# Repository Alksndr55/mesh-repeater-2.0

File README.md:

<div align="center">

# Mesh Repeater

### Плата LoRa-репитера для MeshCore и Meshtastic

**v2.10 · POWER + LOGIC + SHIELD · 90 × 60 мм**

Солнечное питание · Na-ion 1S / LTO 2S · аппаратный watchdog

[Скачать готовый комплект](https://github.com/Alksndr55/mesh-repeater-2.0/releases/download/v2.10/Mesh_Repeater_v2.10_KiCad.zip) · [Релиз v2.10](https://github.com/Alksndr55/mesh-repeater-2.0/releases/tag/v2.10) · [Одноплатная версия v1](https://github.com/Alksndr55/mesh-repeater)

*Mesh Repeater v2.10 в сборе, вариант Na-ion 1S с COLD. Сверху LOGIC, в середине SHIELD, снизу POWER.*

</div>

Mesh Repeater v2 переносит электрическую часть ведущей версии v1 на две рабочие платы размером **90 × 60 мм**. Зарядник и преобразователь питания находятся на POWER, радиочасть и управление — на LOGIC. Между ними предусмотрена отдельная плата экрана SHIELD.

**Главные цели проекта — максимальное энергосбережение и работа в суровых сибирских зимах.**

Такое исполнение уменьшает площадь основания устройства. Межплатное соединение, стойки и крепёж описаны в проекте; исходники KiCad, перечень компонентов и материалы для сборки входят в готовый комплект.

## Что предусмотрено

| Узел | Назначение |
|---|---|
| **nRF52840 + LoRa** | Доработанный NiceNano, модуль HT-RA62 на SX1262, антенный разъём SMA и место под фильтр FL1. |
| **Солнечный зарядник** | CN3722 с настройкой рабочей точки солнечной панели. |
| **Na-ion 1S или LTO 2S** | Три варианта комплектации: Na-ion 1S с COLD, Na-ion 1S без COLD, LTO 2S с пассивной балансировкой. |
| **Питание 3,3 В** | Повышающе-понижающий TPS63802, двухступенчатый LC-фильтр и отдельная ветвь питания радиомодуля. |
| **Контроль аккумулятора** | INA219 измеряет напряжение и ток в основном тракте аккумулятора. |
| **Часы и watchdog** | DS3231M с резервом от CR2032; ATtiny13A следит за активностью TXEN и может сбросить основной процессор. |
| **Подключение и обслуживание** | Разъём внешнего GPS, I²C и UART с логикой 3,3 В, AVR ISP, кнопки USER/RESET и контрольные точки. |

## Три платы одного комплекта

| Плата | Что на ней |
|---|---|
| **POWER** | Заряд аккумулятора, COLD или балансиры LTO, преобразователь 3,3 В и LC-фильтр. |
| **LOGIC** | NiceNano, LoRa-модуль, часы, watchdog и интерфейсы. |
| **SHIELD** | Промежуточная плата экрана с GND-плоскостью и окном межплатного соединителя. |

<details>
<summary><strong>Отдельные платы и виды с двух сторон</strong></summary>

| LOGIC — связь и управление | POWER — заряд и питание |
|:---:|:---:|
|  |  |

*3D-рендеры отдельных плат со стороны компонентов. Комплектацию для выбранного варианта определяет BOM.*

| LOGIC — обратная сторона | POWER — обратная сторона |
|:---:|:---:|
|  |  |

</details>

В собранном устройстве LOGIC обращена компонентами вниз. Используется заданная пара межплатных разъёмов; обычная незеркальная розетка не является заменой J201. Размеры стоек и порядок сборки приведены в [описании механики](v2/docs/MECHANICS_RU.md).

### Опциональный фильтр антенны

На LOGIC предусмотрено место **FL1** для полосового SAW-фильтра **S869M000S003**. Он ослабляет внеполосные сигналы. В полосе 868–870 МГц паспортные потери составляют до 2,5 дБ. Штатный тракт проходит через медную перемычку **NT1**. Перед монтажом FL1 перемычку разрезают по инструкции и ограничивают мощность на входе фильтра до **+13 дБм**.

Рабочая температура этого фильтра **−10…+65 °C**. Для более холодных установок сохраняют штатный обход NT1. [Паспорт фильтра](https://abracon.com/datasheets/AEL-Crystals/PN/S869M000S003.pdf) · [Монтаж FL1](docs/ASSEMBLY_COMMON_RU.md)

## Совместимость с MeshCore и Meshtastic

Радиомодуль HT-RA62 (SX1262 с TCXO) подключён по распиновке **FakeTec / ProMicro nRF52840**. Для обеих версий платы подходят следующие профили прошивок.

| Прошивка | Профиль | Конфигурация |
|---|---|---|
| **MeshCore** | ProMicro nRF52840, сборка `ProMicro_repeater` | [MeshCore ProMicro](https://github.com/meshcore-dev/MeshCore/blob/repeater-v1.18.0/variants/promicro/platformio.ini#L40-L53) |
| **Meshtastic** | NRF52 Pro-micro DIY с TCXO, сборка `nrf52_promicro_diy_tcxo` | [Meshtastic ProMicro TCXO](https://github.com/meshtastic/firmware/blob/v2.7.26.54e0d8d/variants/nrf52840/diy/nrf52_promicro_diy_tcxo/platformio.ini) |

Совместимость проверена по распиновке и конфигурациям сборок. Показания напряжения аккумулятора калибруют под делитель платы **1:2**. Для Na-ion 1S и LTO 2S шкалу процента заряда адаптируют под химию и число ячеек. При подключении внешнего UART к J5 сверяют назначение RX и TX с выбранной прошивкой.

## Варианты сборки

| Вариант | Комплектация |
|---|---|
| **Na-ion 1S · COLD** | Узел температурного ограничения зарядного тока установлен. |
| **Na-ion 1S · без COLD** | Сборка без узла COLD. |
| **LTO · 2S** | Две последовательные ячейки LTO и пассивные балансиры. |

Вариант задаётся номиналами и составом деталей по BOM. Это выбор при сборке, а не переключение химии аккумулятора одной перемычкой. Условия заряда выбирают по паспорту конкретных ячеек; схема LTO не заменяет полноценную BMS.

### COLD — ограничение тока заряда на холоде

В сборке Na-ion 1S с COLD датчик TH1 на POWER задаёт температурный режим солнечного зарядника CN3722. При охлаждении схема включает дополнительный шунт R56 в цепь измерения тока. Расчётный предел зарядного тока снижается примерно с **0,67 А до 0,10 А**. При потеплении возвращается обычный режим.

Расчётный порог снижения тока — **−17,4 °C**, возврата — **−14,5 °C**. Разница между порогами помогает избежать частых переключений при колебаниях температуры. Один датчик TH1 устанавливают на плате или выносят к аккумулятору. Допустимый ток и температуру заряда сверяют с паспортом конкретной ячейки. [Общая инструкция по сборке](docs/ASSEMBLY_COMMON_RU.md)

### Watchdog — автоматический перезапуск репитера

Отдельный ATtiny13A на LOGIC с прошивкой watchdog v1.00 следит за сигналом **TXEN**, который показывает включение передатчика LoRa. Каждое новое включение передатчика запускает отсчёт заново. Между событиями контроллер спит в режиме Power-down. Когда время ожидания истекает, ATtiny13A подаёт импульс RESET на nRF52840. После сброса выбранная прошивка загружается заново и инициализирует радиомодуль.

При 3,3 В и комнатной температуре расчётные ориентиры составляют около **3,5 часа** ожидания и **1,2 секунды** сброса. При длительном молчании радиомодуля или застрявшем высоком TXEN тайм-аут тоже срабатывает. [Подключение и прошивка watchdog](v2/design/watchdog_reference/INTEGRATION_RU.txt)

## От схемы — к детали на плате

В ZIP уже включён **portable NexusBV**. Запуск `START.cmd` открывает меню с CAD и PDF-схемой нужной платы и сборки. Двойной щелчок по обозначению или свободной части тела символа в PDF помогает найти компонент на бордвью.

- Шесть CAD: по **NaIon_COLD** и **LTO_2S** для POWER, LOGIC и SHIELD, с номиналами и DNP. Для SHIELD открывается только CAD.
- PDF-схемы, BOM, инструкции по электрической и механической сборке.
- Проекты KiCad 10 с локальными посадочными местами и всеми используемыми 3D-моделями.
- Watchdog v1.00: исходники, HEX и инструкция прошивки.

## С чего начать

1. Скачайте **Mesh_Repeater_v2.10_KiCad.zip** из [релиза](https://github.com/Alksndr55/mesh-repeater-2.0/releases/tag/v2.10) и полностью распакуйте его.
2. Для просмотра запустите `START.cmd` в Windows; для редактирования откройте [POWER](v2/design/MeshRepeater2_Power/MeshRepeater2_Power.kicad_pro), [LOGIC](v2/design/MeshRepeater2_Logic/MeshRepeater2_Logic.kicad_pro) или [SHIELD](v2/design/MeshRepeater2_Shield/MeshRepeater2_Shield.kicad_pro) в KiCad 10.
3. Выберите вариант аккумулятора и собирайте комплект по [BOM](v2/bom/COMPONENT_BOM.csv), [общей инструкции](docs/ASSEMBLY_COMMON_RU.md) и [описанию механики](v2/docs/MECHANICS_RU.md).

**Перед первым включением:** модуль NiceNano требует указанной в инструкции доработки питания. Перед подключением USB нужно снять шунт **J11**, а вернуть его после отключения USB. J8 и J12 соединены с общей BAT: независимые аккумуляторы к ним одновременно не подключают.

## Документация

[Общая схема PDF](shared/output/pdf/MeshRepeater_schematic.pdf) · [Схема KiCad](shared/schematic/MeshRepeater.kicad_pro) · [Сборка v2](v2/docs/ASSEMBLY_RU.md) · [Аппаратные ограничения](docs/LIMITATIONS_RU.md) · [Изменения выпуска](https://github.com/Alksndr55/mesh-repeater-2.0/releases/tag/v2.10)

<details>
<summary><strong>Статус проекта и проверки</strong></summary>

Это предварительный инженерный выпуск. Для точных файлов v2.10 проверены общая схема, BOM, ERC/DRC, соответствие плат схеме и комплектность архива. Эти проверки не заменяют испытания собранного устройства: дальность связи, автономность, температурные режимы и эффективность экрана здесь не заявляются как измеренные характеристики.

[Отчёт проверок](v2/audit/current/checks.json) · [Экспорт CAD/PDF](v2/audit/current/exports.json) · [Манифест файлов](RELEASE_MANIFEST.json)

</details>

---

**Designed by @Alksndritm** · [Alksndr55](https://github.com/Alksndr55)

Собственные материалы — [CC BY-NC-SA 4.0](v2/LICENSE.md). Сторонние компоненты, модели и программы сохраняют свои лицензии.

Проекты прошивок — [MeshCore](https://github.com/meshcore-dev/MeshCore) и [Meshtastic](https://github.com/meshtastic/firmware).

## Поддержать проект

**Осциллограф Siglent SDS1204X HD.** Пульсации любят прятаться между цифрами мультиметра. Осциллограф поможет их поймать и проверить питание при запуске и передаче.

[Скинуться на осциллограф через Т‑Банк](https://t.tb.ru/pm_short/89zrJmEhG7B)

**Микроскоп Leica IVESTA 3.** У припоя иногда свой план монтажа. Под микроскопом удобнее паять мелкие детали и вовремя замечать перемычки между выводами.

[Скинуться на микроскоп через Сбер](https://messenger.sbrf.ru/sl/KsiFZJu4xBxTLGTPz)

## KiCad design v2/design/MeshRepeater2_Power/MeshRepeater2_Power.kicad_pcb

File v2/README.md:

# Mesh Repeater v2.10

Designed by @Alksndritm. Текущее исполнение общего проекта.
Электрические изменения следуют ведущей v1; разводка адаптирована к двум платам.
Предыдущий опубликованный выпуск от 30.10.2026: [v2.09 на GitHub](https://github.com/Alksndr55/mesh-repeater-2.0/releases/tag/v2.09).
Предыдущая публикация — [v2.06](https://github.com/Alksndr55/mesh-repeater-2.0/releases/tag/v2.06)
(прежнее обозначение A6). Локальная редакция от 06.11.2026 — v2.10. Следующий номер — v2.11.

[POWER](design/MeshRepeater2_Power/MeshRepeater2_Power.kicad_pro) · [LOGIC](design/MeshRepeater2_Logic/MeshRepeater2_Logic.kicad_pro) · [SHIELD](design/MeshRepeater2_Shield/MeshRepeater2_Shield.kicad_pro)

[Общая схема](../shared/schematic/MeshRepeater.kicad_pro) ·
[BOM](bom/COMPONENT_BOM.csv) · [Сборка](docs/ASSEMBLY_RU.md) ·
[Порядок выпуска](../docs/WORKFLOW_RU.md) · [Лицензия](LICENSE.md).

Текущие экспорты находятся в output/current, проверки — в audit/current.
Версия и состав задаются корневым project.json. CAD остаётся редактируемым;
общий процесс выпуска сохраняет геометрию и проверяет соответствие общей схеме.
Опубликованные исторические теги сохраняют свои прежние имена.

Дорожки и GND-переходы приведены к [общим правилам](../docs/ROUTING_RULES_RU.md)
с адаптацией к POWER/LOGIC. Включён [watchdog v1.00](design/watchdog_reference/INTEGRATION_RU.txt)
с каноническими исходником и HEX; LFUSE=0x73, HFUSE=0xFB, ISP 100 мкс.
Локальный архив этого выпуска создаётся в `../releases/v2.10/`.
[Результат разводки и исключения сетки](../docs/ROUTING_RESULT_RU.md).

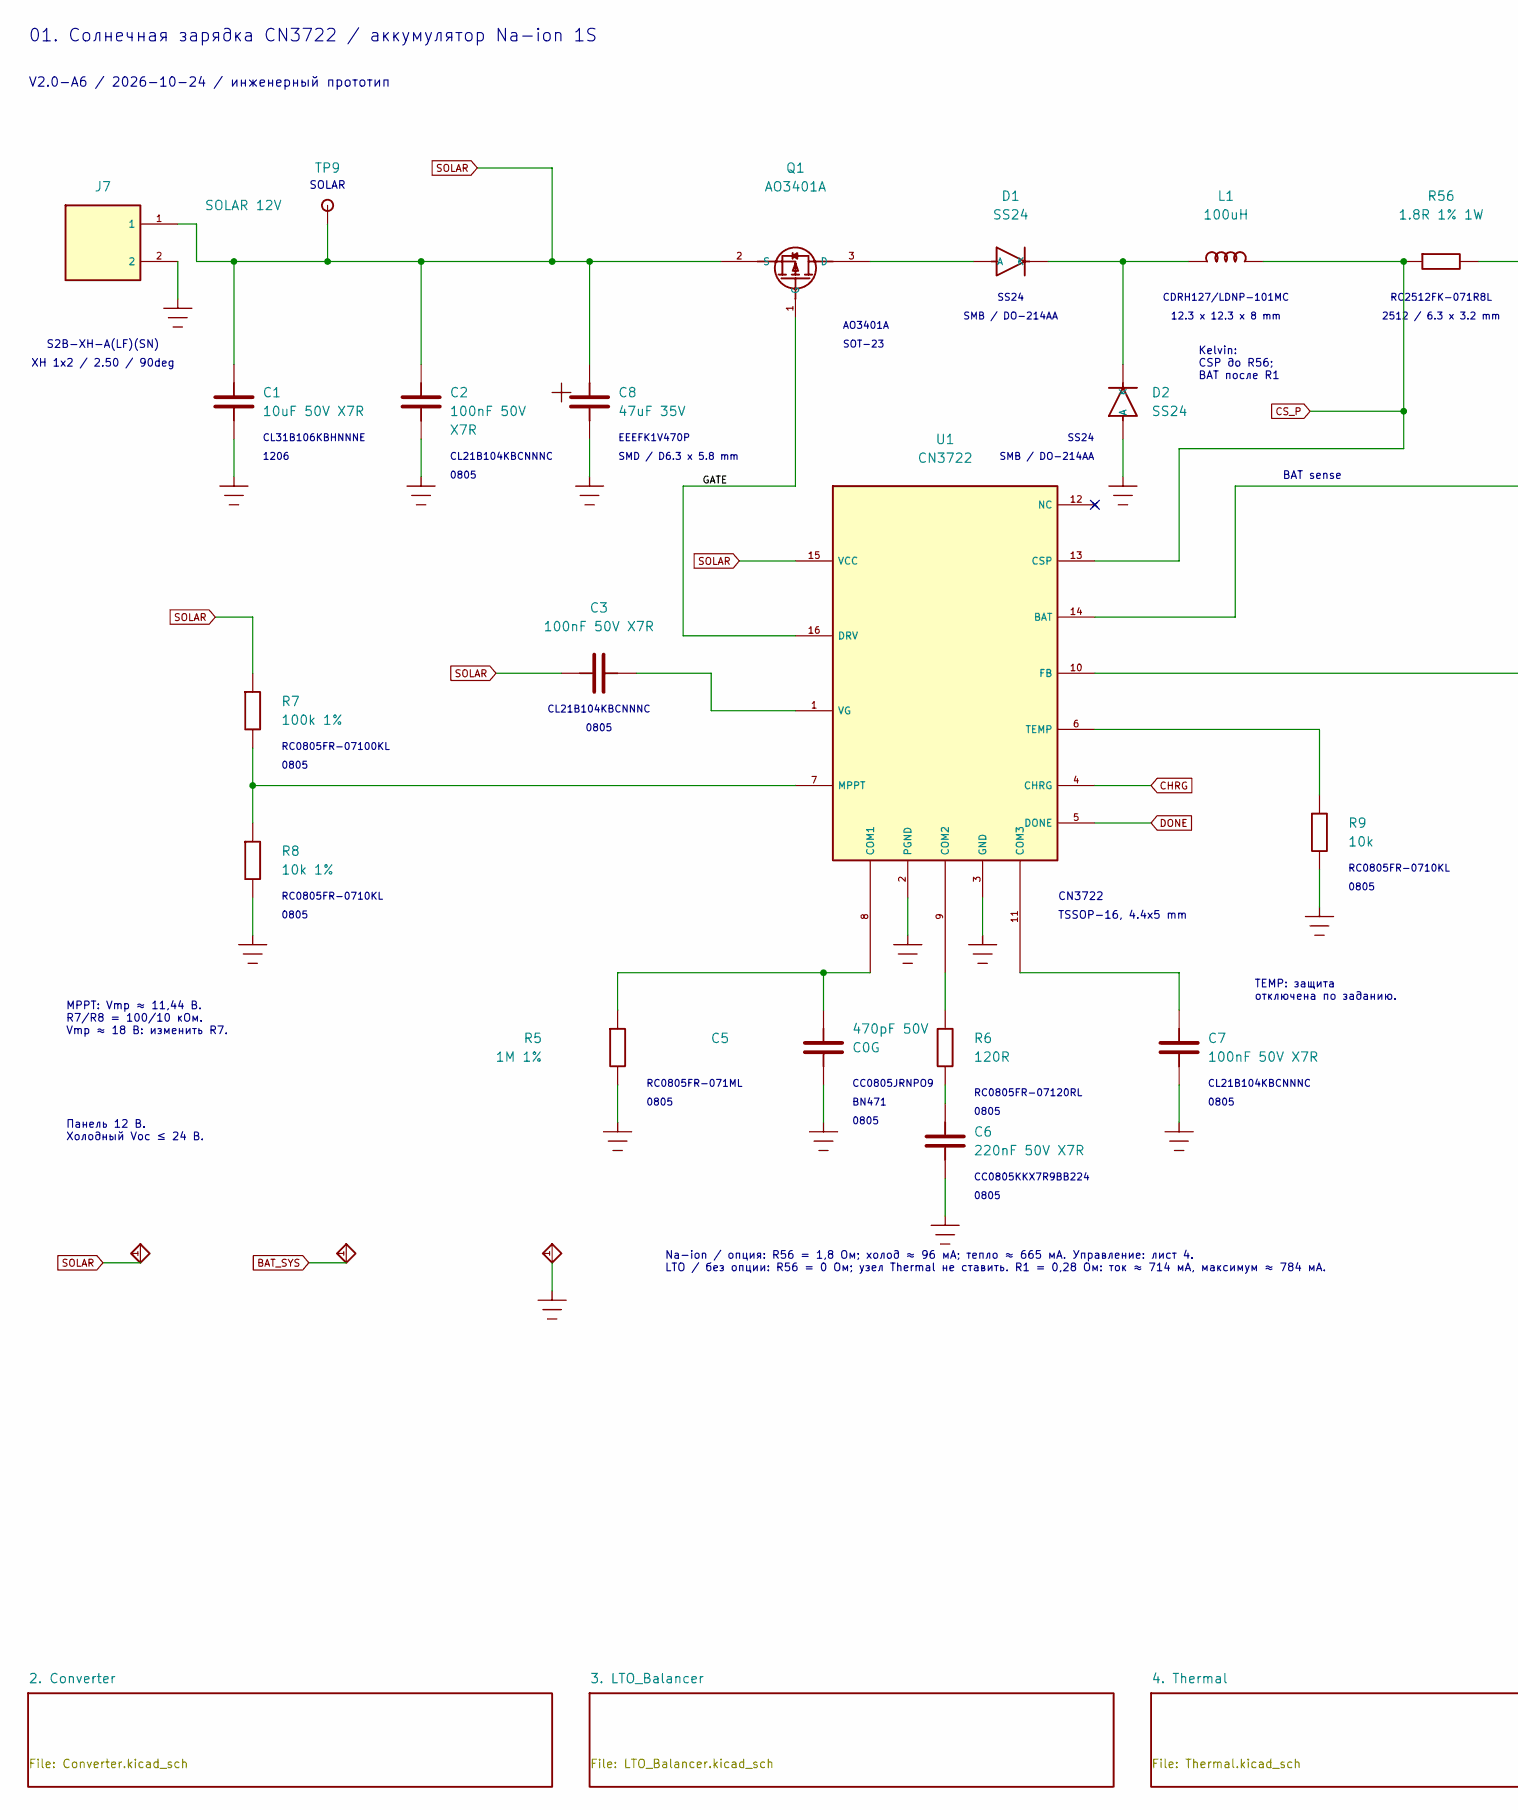
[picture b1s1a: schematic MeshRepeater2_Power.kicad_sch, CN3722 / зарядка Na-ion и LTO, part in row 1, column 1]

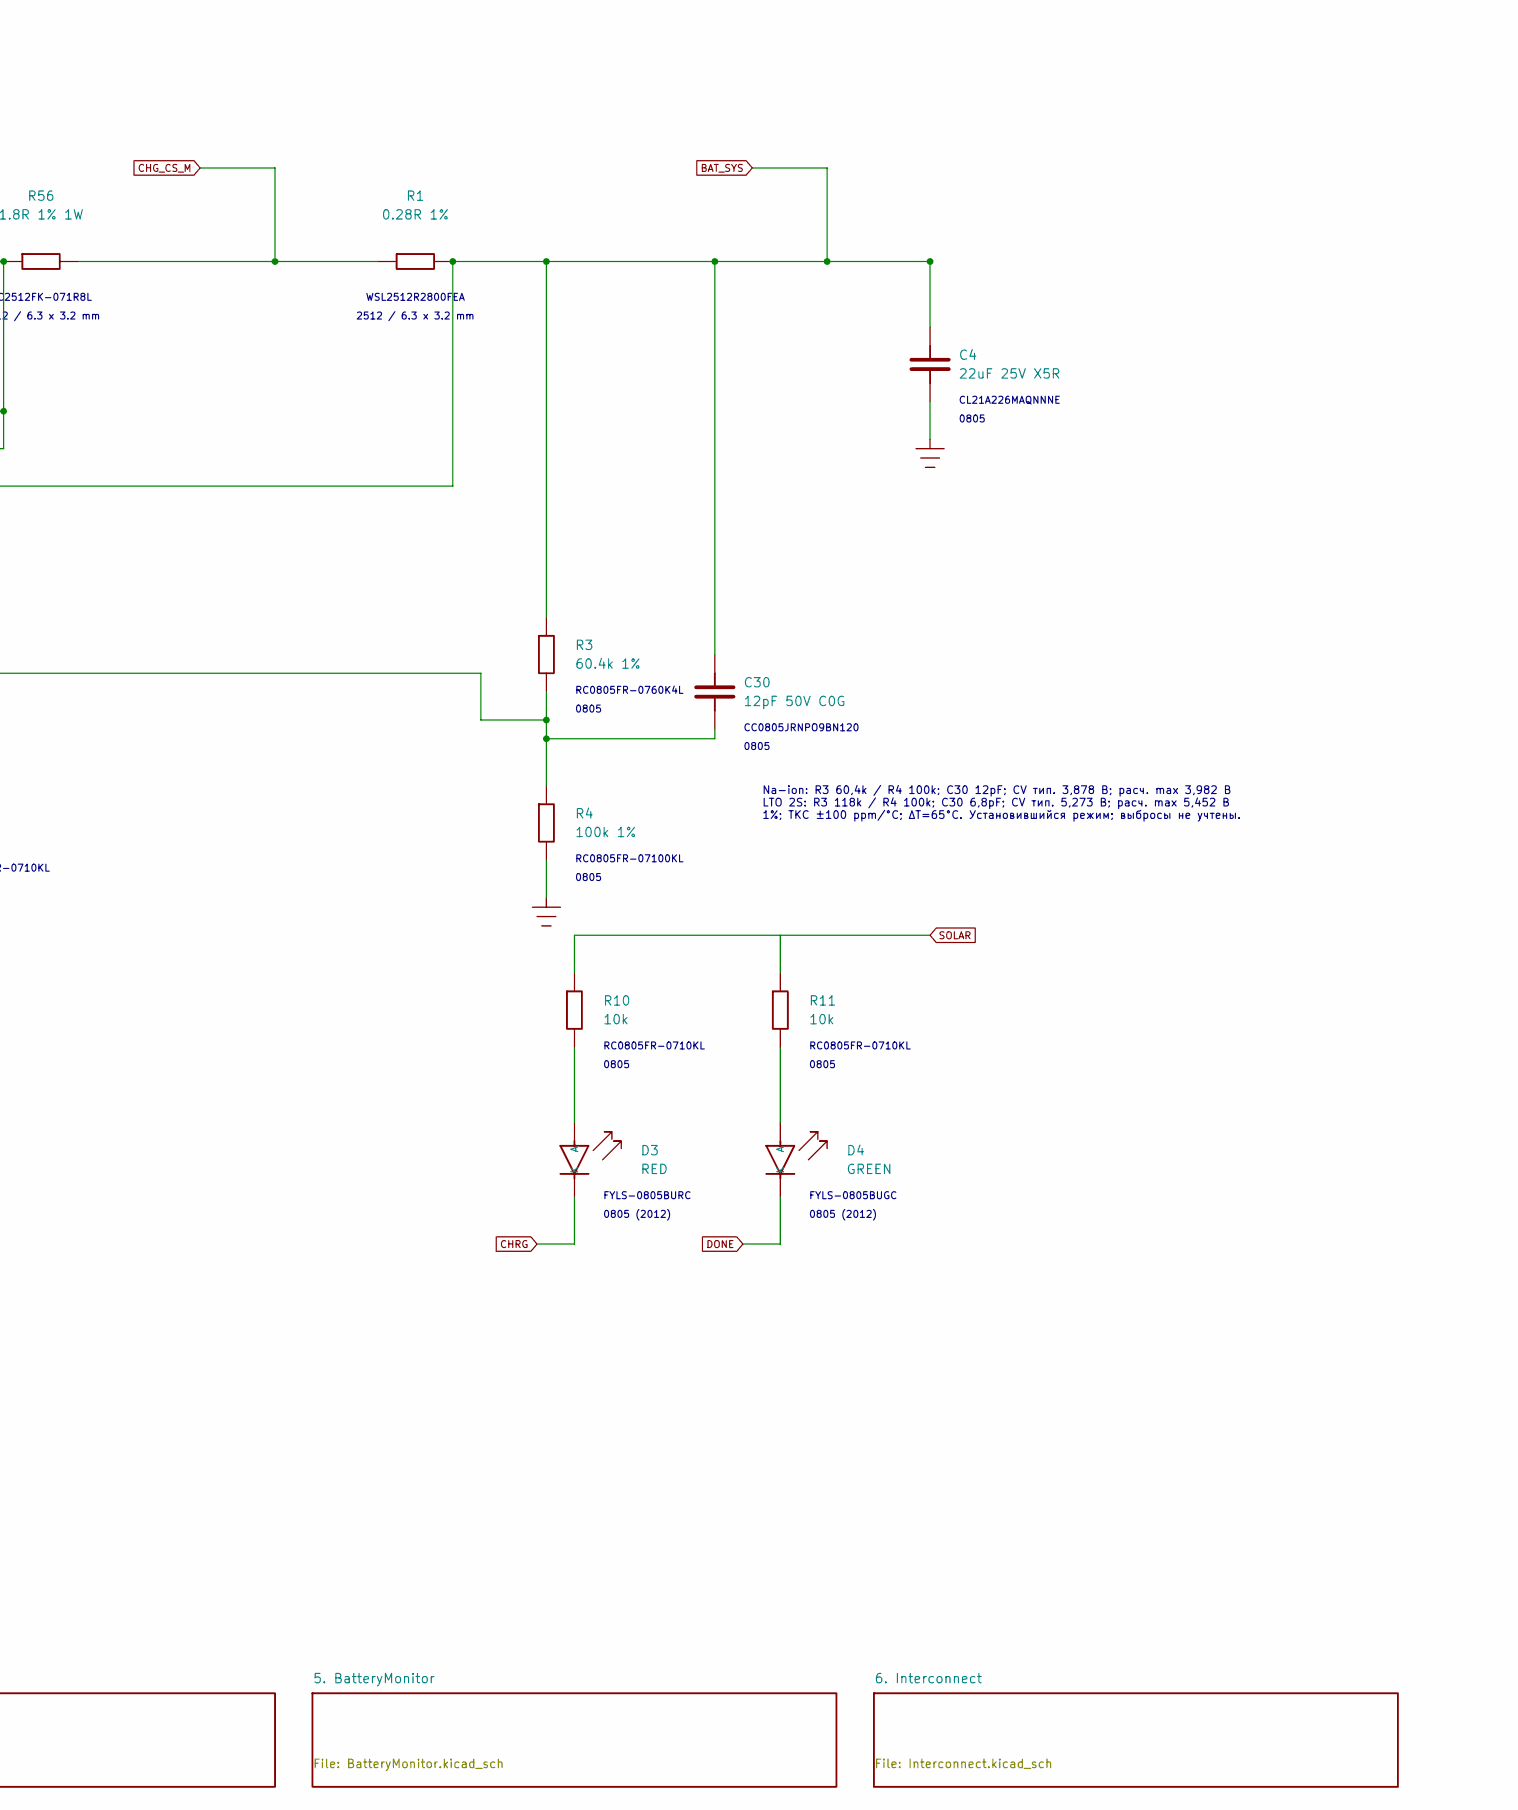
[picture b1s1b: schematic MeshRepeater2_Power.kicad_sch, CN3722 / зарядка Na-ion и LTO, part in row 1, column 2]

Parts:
C1: 10uF 50V X7R; C_1206_3216Metric__V2_C1; MPN CL31B106KBHNNNE
C2: 100nF 50V X7R; C_0805_2012Metric__V2_C2; MPN CL21B104KBCNNNC
C3: 100nF 50V X7R; C_0805_2012Metric__V2_C3; MPN CL21B104KBCNNNC
C4: 22uF 25V X5R; C_0805_2012Metric__V2_C4; MPN CL21A226MAQNNNE
C5: 470pF 50V C0G; C_0805_2012Metric__V2_C5; MPN CC0805JRNPO9BN471
C6: 220nF 50V X7R; C_0805_2012Metric__V2_C6; MPN CC0805KKX7R9BB224
C7: 100nF 50V X7R; C_0805_2012Metric__V2_C7; MPN CL21B104KBCNNNC
C8: 47uF 35V; CP_Elec_Panasonic_FK_D_6.3x5.8__V2_C8; MPN EEEFK1V470P
C30: 12pF 50V C0G; C_0805_2012Metric__V2_C30; MPN CC0805JRNPO9BN120
D1: SS24; D_SMB__V2_D1; MPN SS24
D2: SS24; D_SMB__V2_D2; MPN SS24
D3: RED; LED_0805_2012Metric__V2_D3; MPN FYLS-0805BURC
D4: GREEN; LED_0805_2012Metric__V2_D4; MPN FYLS-0805BUGC
J7: SOLAR 12V; JST_XH_S2B-XH-A_1x02_P2.50mm_Horizontal__V2_J7; MPN JST S2B-XH-A(LF)(SN)
L1: 100uH; L_Sumida_CDRH127_LDNP_101MC__V2_L1; MPN CDRH127/LDNP-101MC
Q1: AO3401A; SOT-23__V2_Q1; MPN AO3401A
R1: 0.28R 1%; R_Vishay_WSL2512_A3__A3_R1; MPN WSL2512R2800FEA; LCSC C5710536
R3: 60.4k 1%; R_0805_2012Metric__V2_R3; MPN RC0805FR-0760K4L; LCSC C2084414
R4: 100k 1%; R_0805_2012Metric__V2_R4; MPN RC0805FR-07100KL; LCSC C110775
R5: 1M 1%; R_0805_2012Metric__V2_R5; MPN RC0805FR-071ML
R6: 120R; R_0805_2012Metric__V2_R6; MPN RC0805FR-07120RL
R7: 100k 1%; R_0805_2012Metric__V2_R7; MPN RC0805FR-07100KL; LCSC C856623
R8: 10k 1%; R_0805_2012Metric__V2_R8; MPN RC0805FR-0710KL
R9: 10k; R_0805_2012Metric__V2_R9; MPN RC0805FR-0710KL
R10: 10k; R_0805_2012Metric__V2_R10; MPN RC0805FR-0710KL
R11: 10k; R_0805_2012Metric__V2_R11; MPN RC0805FR-0710KL
R56: 1.8R 1% 1W; R_2512_6332Metric__A3_R56; MPN RC2512FK-071R8L
TP9: SOLAR; TestPoint_Pad_D1p5mm_A3_Edge_R0p9; MPN PCB test pad / not purchased
U1: CN3722; TSSOP-16_4.4x5mm_P0.65mm__V2_U1; MPN CN3722; LCSC C77905

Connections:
/GATE: Q1.1 (G), U1.16 (DRV)
BAT_SYS: C4.1, C30.1, R1.2, R3.1, U1.14 (BAT); also elsewhere on the board
CHG_CS_M: R1.1, R56.2; also elsewhere on the board
CHRG: D3.1 (K), U1.4 (CHRG)
CS_P: L1.2, R56.1, U1.13 (CSP); also elsewhere on the board
DONE: D4.1 (K), U1.5 (DONE)
GND: C1.2, C2.2, C4.2, C5.2, C6.2, C7.2, C8.2, D2.2 (A), J7.2, R4.2, R5.2, R8.2, R9.2, U1.2 (PGND), U1.3 (GND); also elsewhere on the board
unnamed: C6.1, R6.2
unnamed: D1.2 (A), Q1.3 (D)
unnamed: D1.1 (K), D2.1 (K), L1.1
unnamed: D3.2 (A), R10.2
unnamed: D4.2 (A), R11.2
unnamed: C5.1, R5.1, U1.8 (COM1)
unnamed: R6.1, U1.9 (COM2)
unnamed: C7.1, U1.11 (COM3)
unnamed: C30.2, R3.2, R4.1, U1.10 (FB)
unnamed: R7.2, R8.1, U1.7 (MPPT)
unnamed: R9.1, U1.6 (TEMP)
unnamed: C3.2, U1.1 (VG)
SOLAR: C1.1, C2.1, C3.1, C8.1, J7.1, Q1.2 (S), R7.1, R10.1, R11.1, TP9.1, U1.15 (VCC); also elsewhere on the board

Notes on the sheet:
0805
0805 (2012)
2512 / 6.3 x 3.2 mm
XH 1x2 / 2.50 / 90deg
Kelvin: CSP до R56; BAT после R1
CL21B104KBCNNNC
EEEFK1V470P
RC0805FR-0710KL
Панель 12 В. Холодный Voc ≤ 24 В.
RC0805FR-07100KL
FYLS-0805BUGC
MPPT: Vmp ≈ 11,44 В. R7/R8 = 100/10 кОм. Vmp ≈ 18 В: изменить R7.
RC0805FR-071ML
CDRH127/LDNP-101MC
CL31B106KBHNNNE
SS24
01. Солнечная зарядка CN3722 / аккумулятор Na-ion 1S
FYLS-0805BURC
S2B-XH-A(LF)(SN)
CC0805JRNPO9
RC2512FK-071R8L
1206
CN3722
WSL2512R2800FEA
V2.0-A6 / 2026-10-24 / инженерный прототип
Na-ion: R3 60,4k / R4 100k; C30 12pF; CV тип. 3,878 В; расч. max 3,982 В LTO 2S: R3 118k / R4 100k; C30 6,8pF; CV тип. 5,273 В; расч. max 5,452 В 1%; ТКС ±100 ppm/°C; ΔT=65°C. Установившийся режим; выбросы не учтены.
Na-ion / опция: R56 = 1,8 Ом; холод ≈ 96 мА; тепло ≈ 665 мА. Управление: лист 4. LTO / без опции: R56 = 0 Ом; узел Thermal не ставить. R1 = 0,28 Ом: ток ≈ 714 мА, максимум ≈ 784 мА.
BAT sense
SOT-23
CL21A226MAQNNNE
RC0805FR-0760K4L
RC0805FR-07120RL
TEMP: защита отключена по заданию.
SOLAR
TSSOP-16, 4.4x5 mm
SMD / D6.3 x 5.8 mm
SMB / DO-214AA
CC0805KKX7R9BB224
BN471
AO3401A

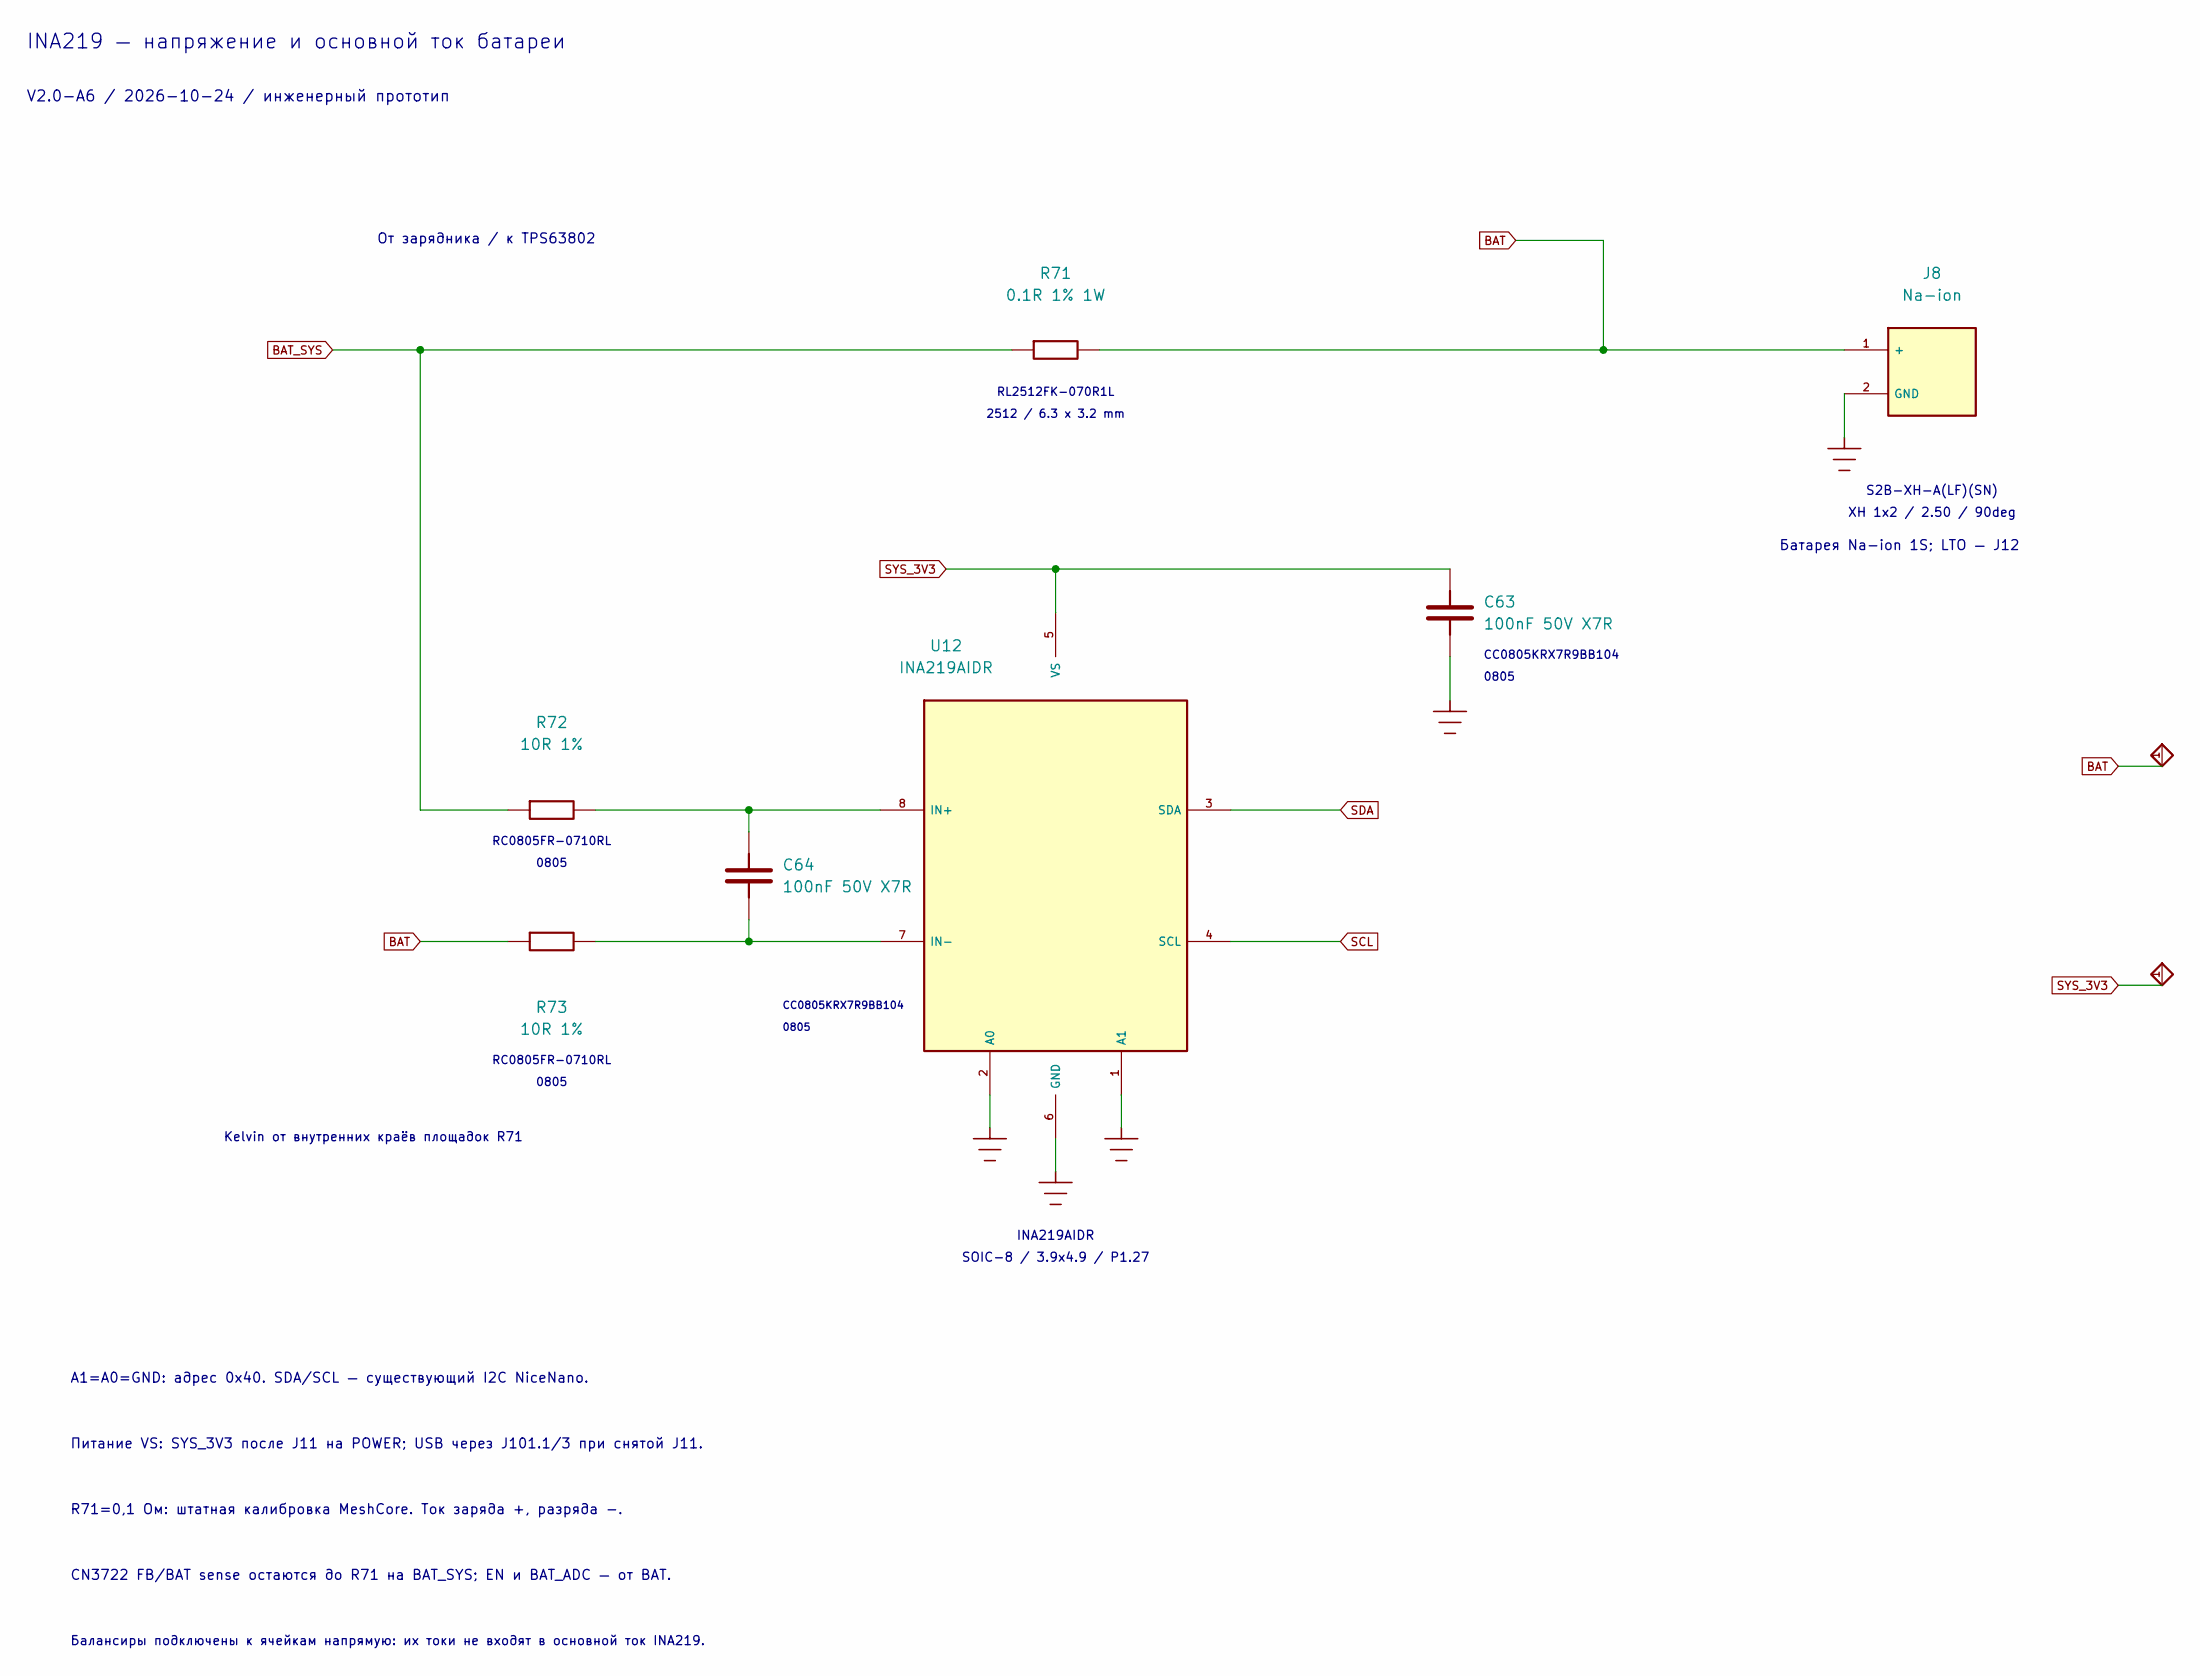
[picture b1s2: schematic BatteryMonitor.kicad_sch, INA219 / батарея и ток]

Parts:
C63: 100nF 50V X7R; C_0805_2012Metric__V2_C63; MPN CC0805KRX7R9BB104
C64: 100nF 50V X7R; C_0805_2012Metric__V2_C64; MPN CC0805KRX7R9BB104
J8: Na-ion; JST_XH_S2B-XH-A_1x02_P2.50mm_Horizontal__V2_J8; MPN JST S2B-XH-A(LF)(SN)
R71: 0.1R 1% 1W; R_2512_6332Metric__A3_R71; MPN RL2512FK-070R1L
R72: 10R 1%; R_0805_2012Metric__V2_R72; MPN RC0805FR-0710RL
R73: 10R 1%; R_0805_2012Metric__V2_R73; MPN RC0805FR-0710RL
U12: INA219AIDR; SOIC-8_3.9x4.9mm_P1.27mm__V2_U12; MPN INA219AIDR

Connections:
BAT: J8.1 (+), R71.2, R73.1; also elsewhere on the board
BAT_SYS: R71.1, R72.1; also elsewhere on the board
GND: C63.2, J8.2 (GND), U12.1 (A1), U12.2 (A0), U12.6 (GND); also elsewhere on the board
unnamed: C64.1, R72.2, U12.8 (IN+)
unnamed: C64.2, R73.2, U12.7 (IN-)
SCL: U12.4 (SCL); also elsewhere on the board
SDA: U12.3 (SDA); also elsewhere on the board
SYS_3V3: C63.1, U12.5 (VS); also elsewhere on the board

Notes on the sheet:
CC0805KRX7R9BB104
От зарядника / к TPS63802
R71=0,1 Ом: штатная калибровка MeshCore. Ток заряда +, разряда −.
RC0805FR-0710RL
XH 1x2 / 2.50 / 90deg
0805
CN3722 FB/BAT sense остаются до R71 на BAT_SYS; EN и BAT_ADC — от BAT.
SOIC-8 / 3.9x4.9 / P1.27
Балансиры подключены к ячейкам напрямую: их токи не входят в основной ток INA219.
A1=A0=GND: адрес 0x40. SDA/SCL — существующий I2C NiceNano.
RL2512FK-070R1L
V2.0-A6 / 2026-10-24 / инженерный прототип
INA219 — напряжение и основной ток батареи
Питание VS: SYS_3V3 после J11 на POWER; USB через J101.1/3 при снятой J11.
INA219AIDR
Kelvin от внутренних краёв площадок R71
S2B-XH-A(LF)(SN)
Батарея Na-ion 1S; LTO — J12
2512 / 6.3 x 3.2 mm

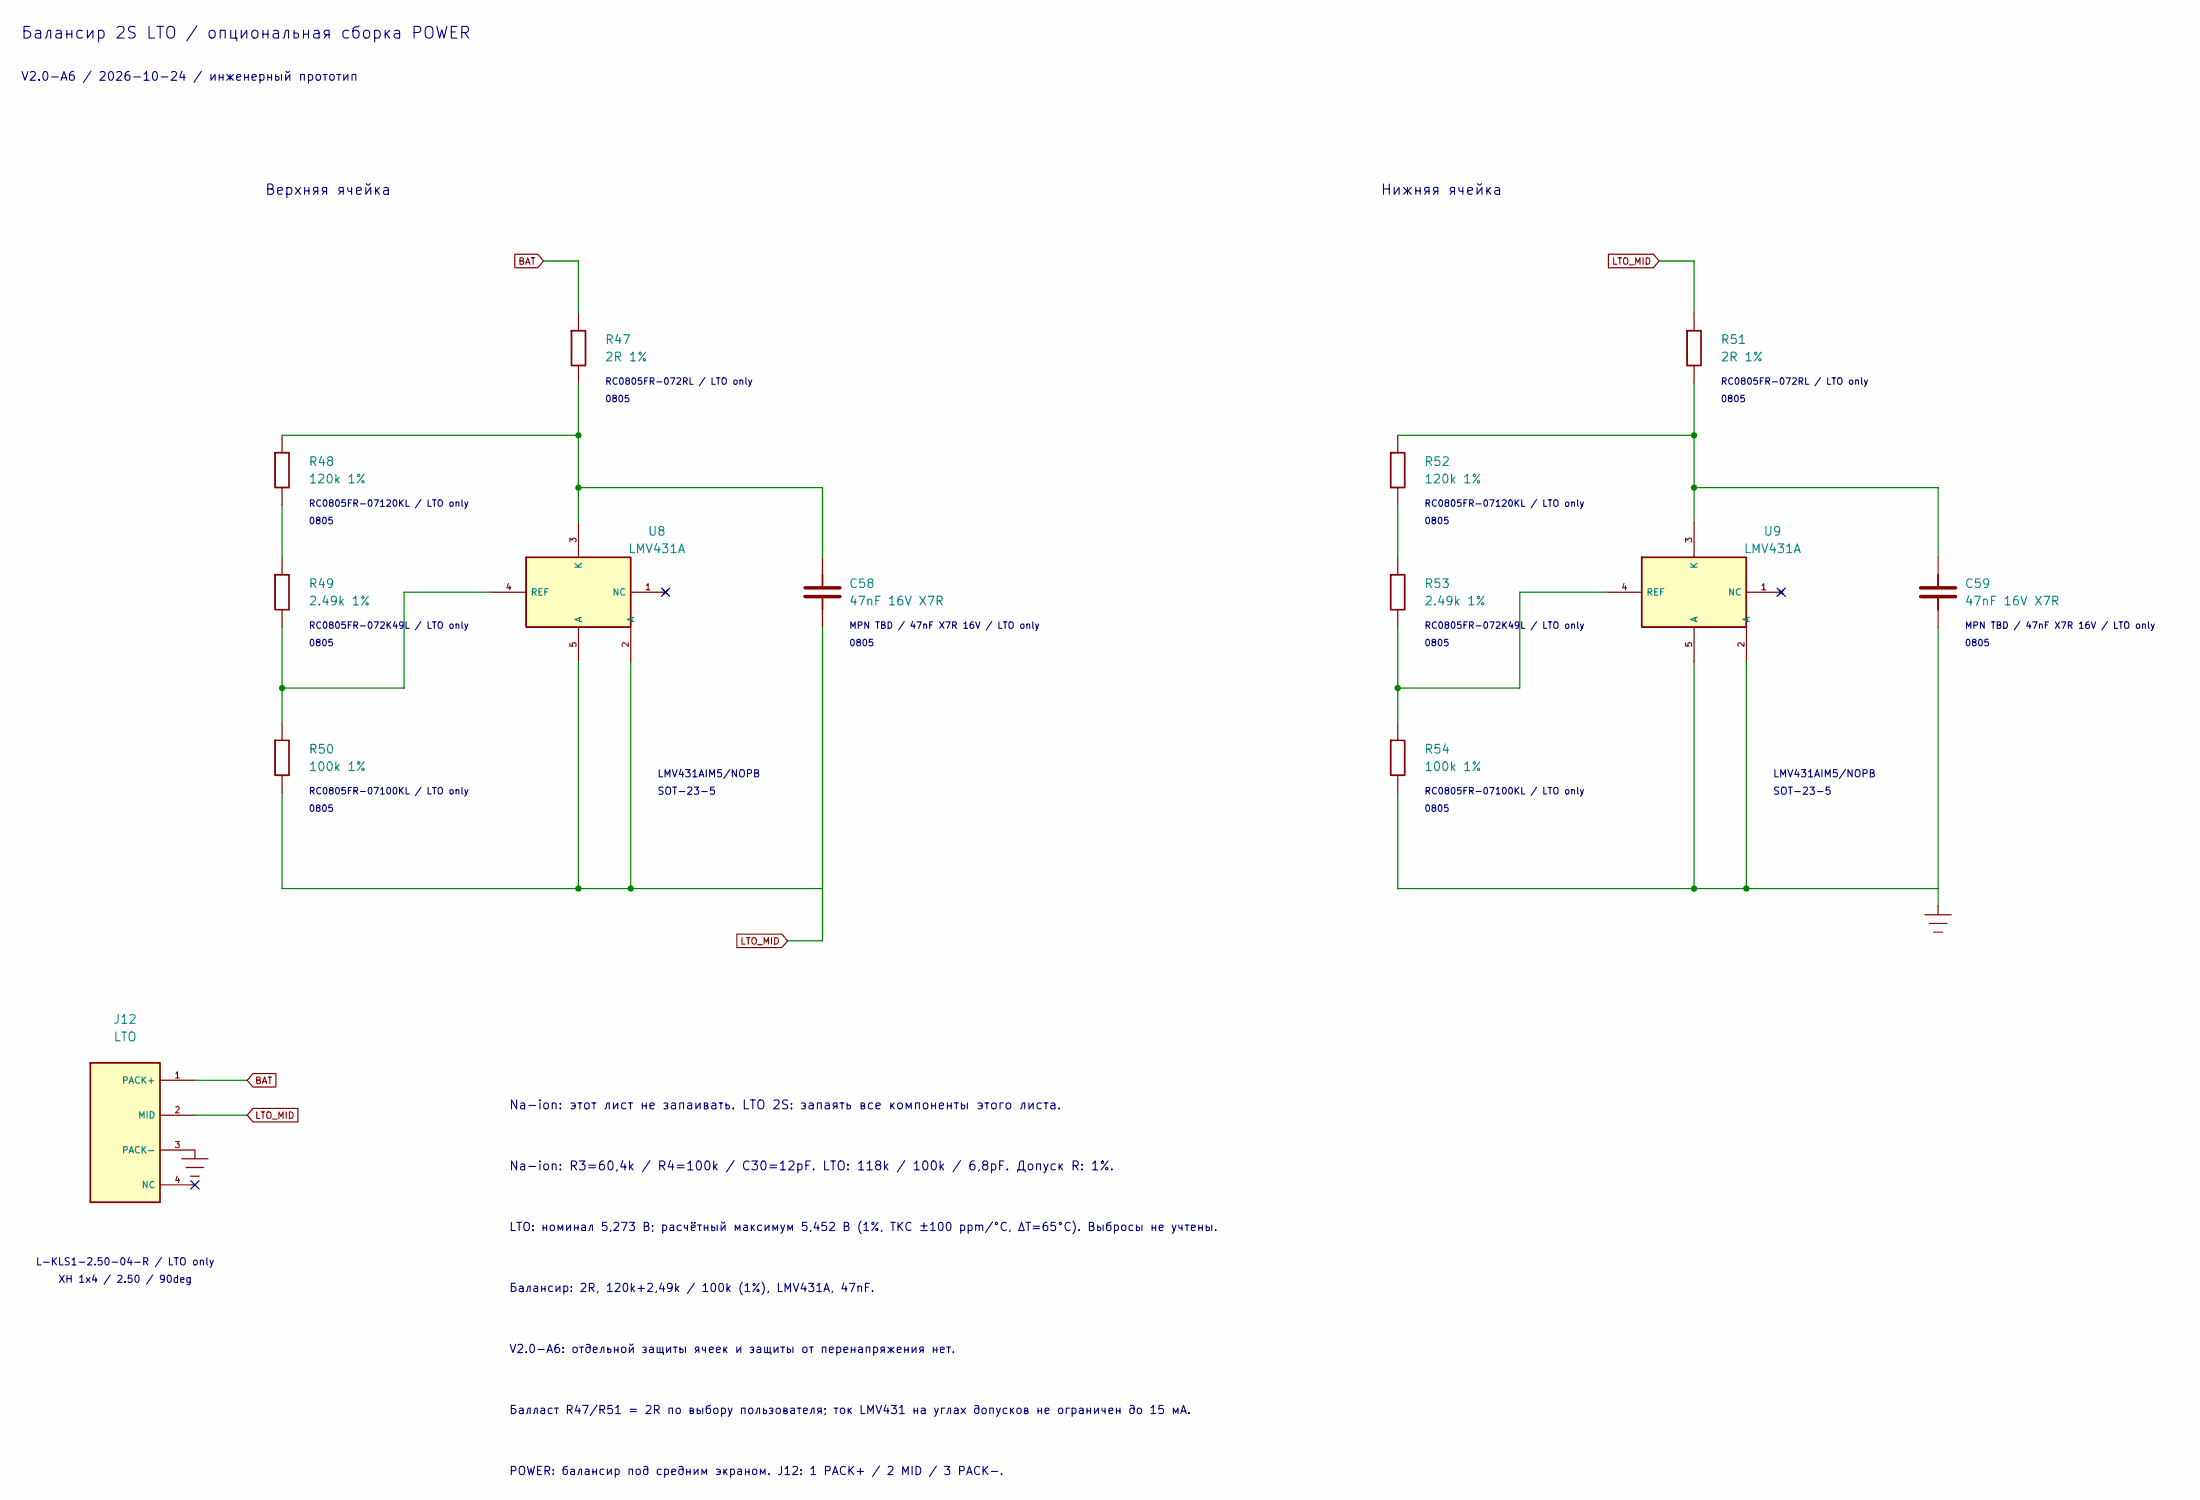
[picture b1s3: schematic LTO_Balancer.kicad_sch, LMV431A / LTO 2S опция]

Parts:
C58: 47nF 16V X7R; C_0805_2012Metric__V2_C58; MPN MPN TBD / 47nF X7R 16V
C59: 47nF 16V X7R; C_0805_2012Metric__V2_C59; MPN MPN TBD / 47nF X7R 16V
J12: LTO; KLS_XH_L_KLS1_2_50_04_R_Horizontal__V2_J12; MPN KLS L-KLS1-2.50-04-R
R47: 2R 1%; R_0805_2012Metric__V2_R47; MPN RC0805FR-072RL; LCSC C110775
R48: 120k 1%; R_0805_2012Metric__V2_R48; MPN RC0805FR-07120KL; LCSC C110775
R49: 2.49k 1%; R_0805_2012Metric__V2_R49; MPN RC0805FR-072K49L; LCSC C110775
R50: 100k 1%; R_0805_2012Metric__V2_R50; MPN RC0805FR-07100KL; LCSC C110775
R51: 2R 1%; R_0805_2012Metric__V2_R51; MPN RC0805FR-072RL; LCSC C110775
R52: 120k 1%; R_0805_2012Metric__V2_R52; MPN RC0805FR-07120KL; LCSC C110775
R53: 2.49k 1%; R_0805_2012Metric__V2_R53; MPN RC0805FR-072K49L; LCSC C110775
R54: 100k 1%; R_0805_2012Metric__V2_R54; MPN RC0805FR-07100KL; LCSC C110775
U8: LMV431A; SOT-23-5__V2_U8; MPN LMV431AIM5/NOPB
U9: LMV431A; SOT-23-5__V2_U9; MPN LMV431AIM5/NOPB

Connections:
BAT: J12.1 (PACK+), R47.1; also elsewhere on the board
GND: C59.2, J12.3 (PACK-), R54.2, U9.2 (A), U9.5 (A); also elsewhere on the board
LTO_MID: C58.2, J12.2 (MID), R50.2, R51.1, U8.2 (A), U8.5 (A)
unnamed: R48.2, R49.1
unnamed: R52.2, R53.1
unnamed: C58.1, R47.2, R48.1, U8.3 (K)
unnamed: R49.2, R50.1, U8.4 (REF)
unnamed: C59.1, R51.2, R52.1, U9.3 (K)
unnamed: R53.2, R54.1, U9.4 (REF)

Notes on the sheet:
POWER: балансир под средним экраном. J12: 1 PACK+ / 2 MID / 3 PACK-.
V2.0-A6: отдельной защиты ячеек и защиты от перенапряжения нет.
MPN TBD / 47nF X7R 16V / LTO only
Балансир: 2R, 120k+2,49k / 100k (1%), LMV431A, 47nF.
Нижняя ячейка
Балласт R47/R51 = 2R по выбору пользователя; ток LMV431 на углах допусков не ограничен до 15 мА.
0805
Na-ion: этот лист не запаивать. LTO 2S: запаять все компоненты этого листа.
RC0805FR-072RL / LTO only
SOT-23-5
LMV431AIM5/NOPB
RC0805FR-07100KL / LTO only
RC0805FR-07120KL / LTO only
RC0805FR-072K49L / LTO only
Верхняя ячейка
Na-ion: R3=60,4k / R4=100k / C30=12pF. LTO: 118k / 100k / 6,8pF. Допуск R: 1%.
XH 1x4 / 2.50 / 90deg
L-KLS1-2.50-04-R / LTO only
Балансир 2S LTO / опциональная сборка POWER
V2.0-A6 / 2026-10-24 / инженерный прототип
LTO: номинал 5,273 В; расчётный максимум 5,452 В (1%, ТКС ±100 ppm/°C, ΔT=65°C). Выбросы не учтены.
